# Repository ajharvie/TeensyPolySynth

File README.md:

A digital polysynth based on the teensy 4.1

Code heavily adapted from  Albert Nyström's 6-voice teensy synth: https://github.com/albnys/TeensyPoly6

I'll write up the new features and improvements at some point but I promise it's dead good

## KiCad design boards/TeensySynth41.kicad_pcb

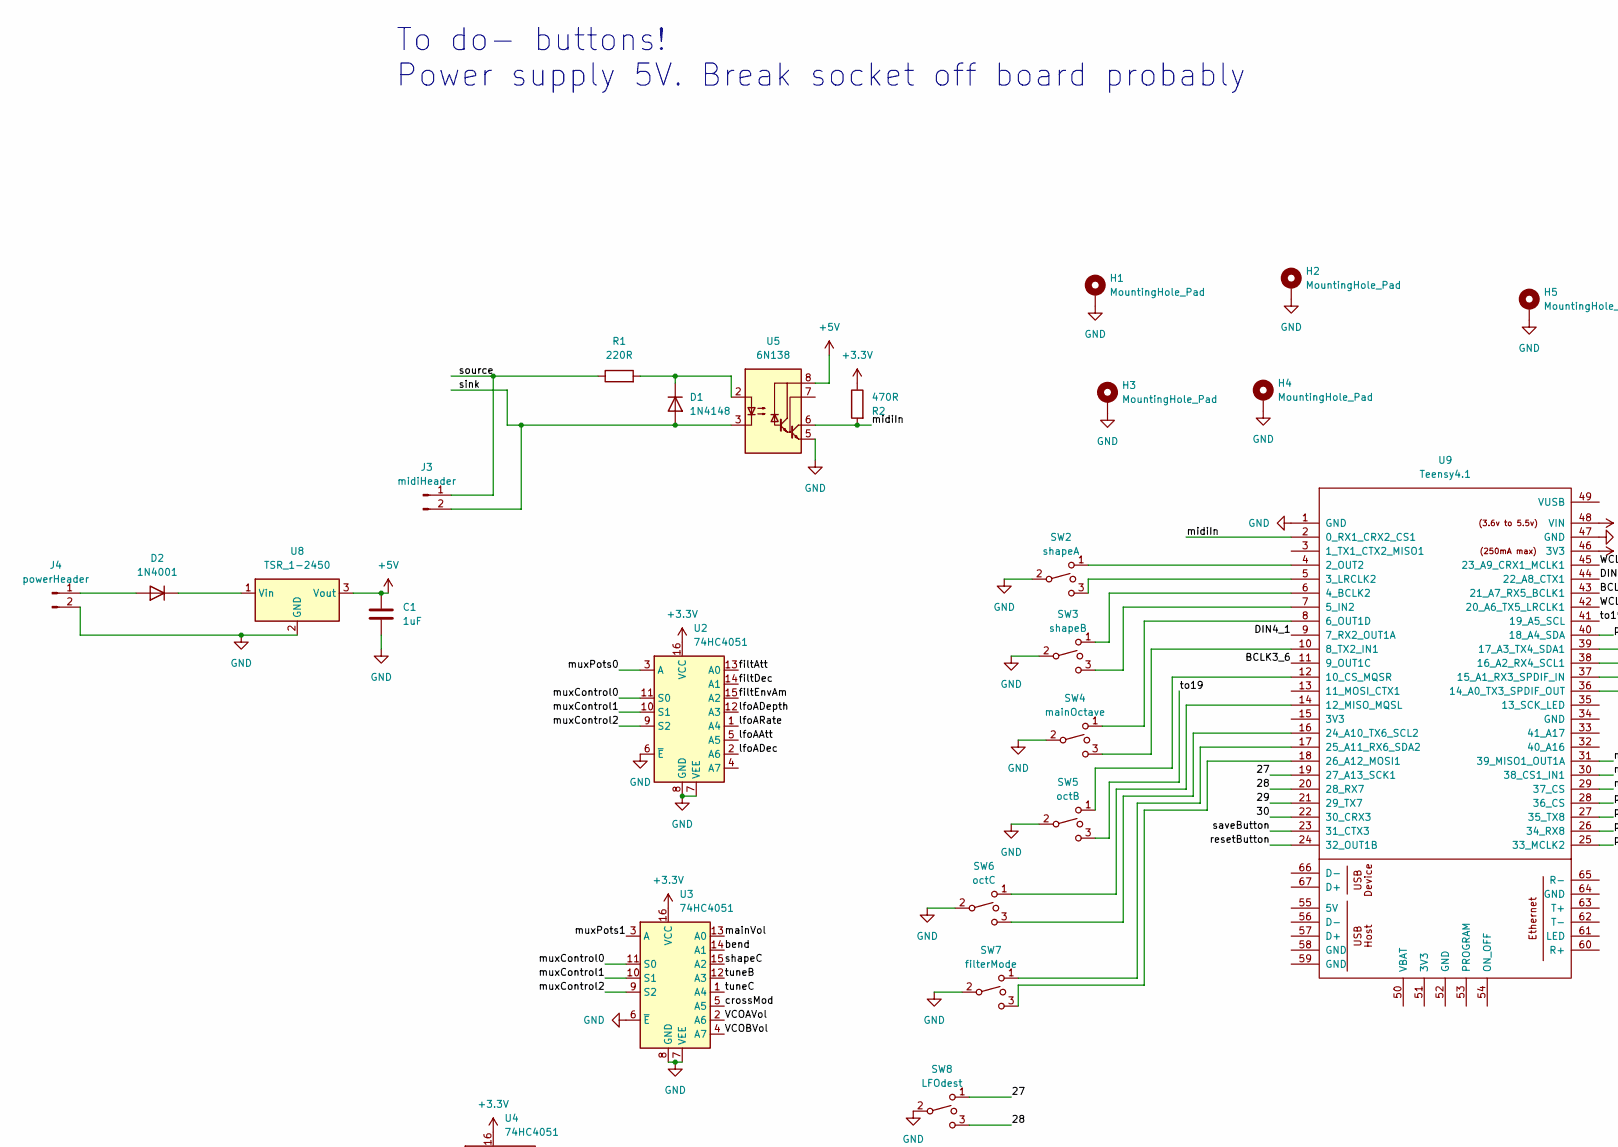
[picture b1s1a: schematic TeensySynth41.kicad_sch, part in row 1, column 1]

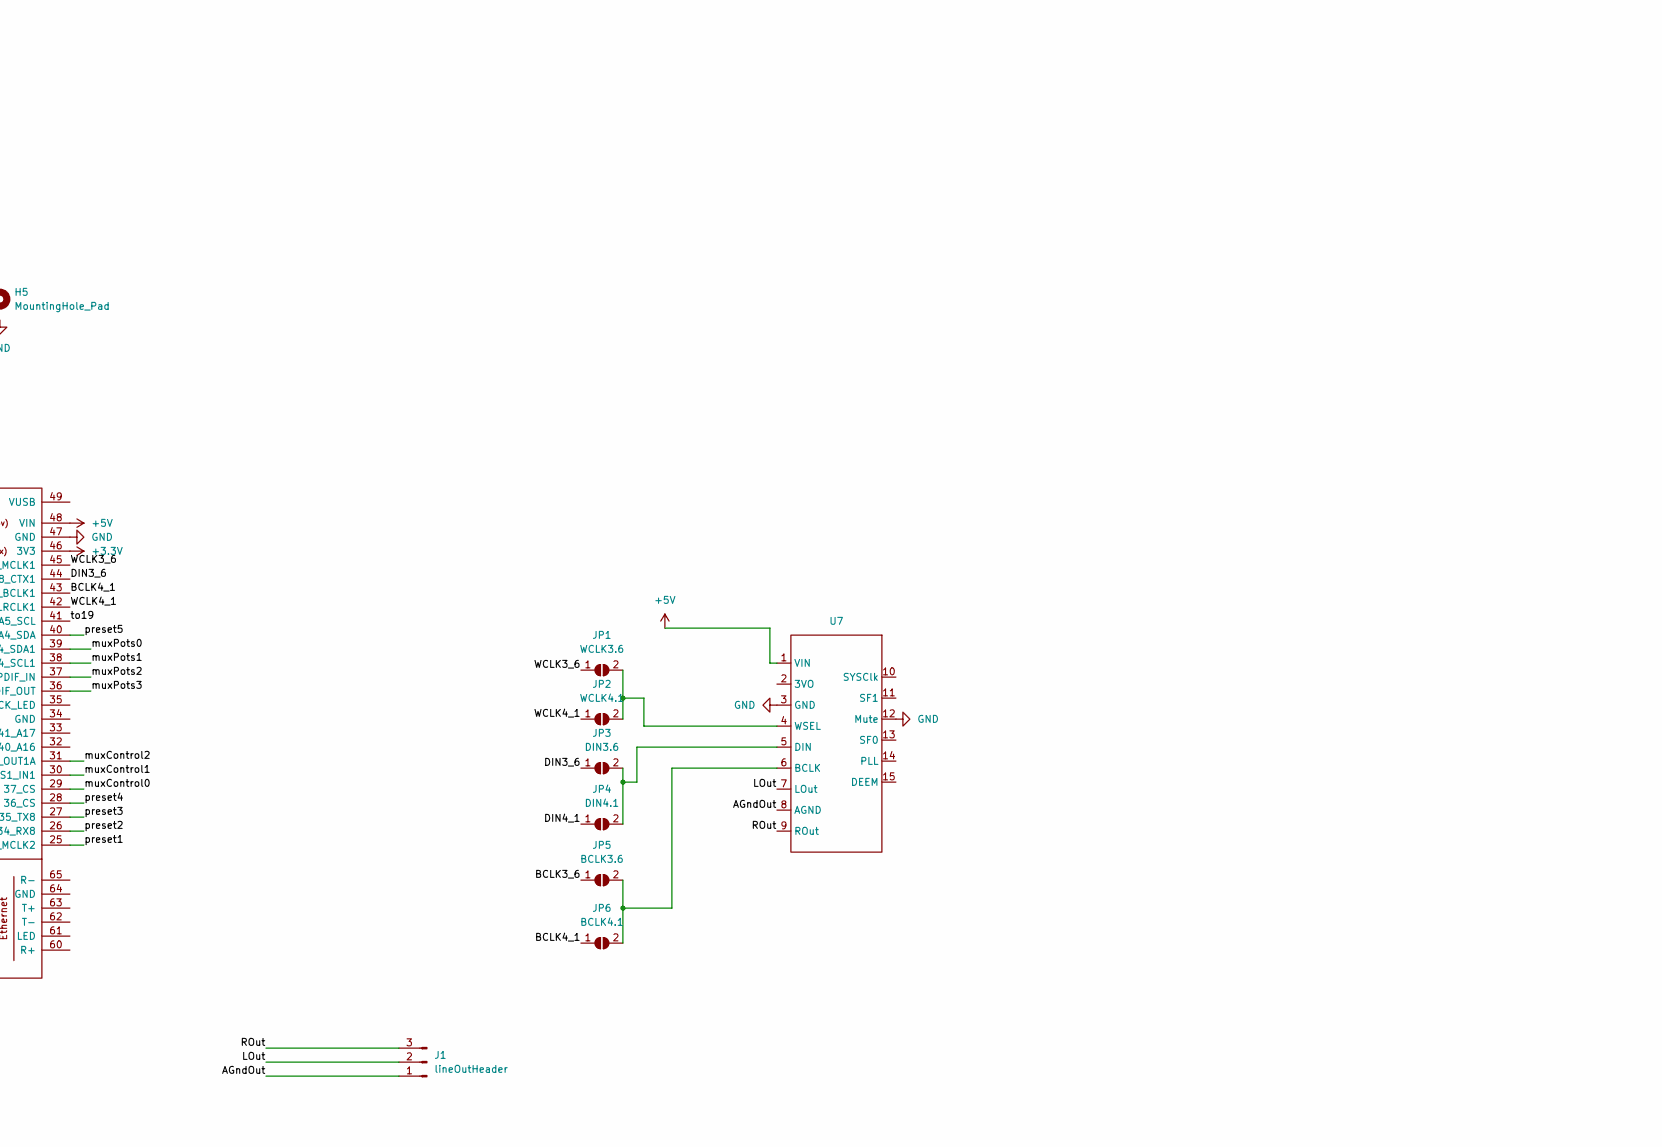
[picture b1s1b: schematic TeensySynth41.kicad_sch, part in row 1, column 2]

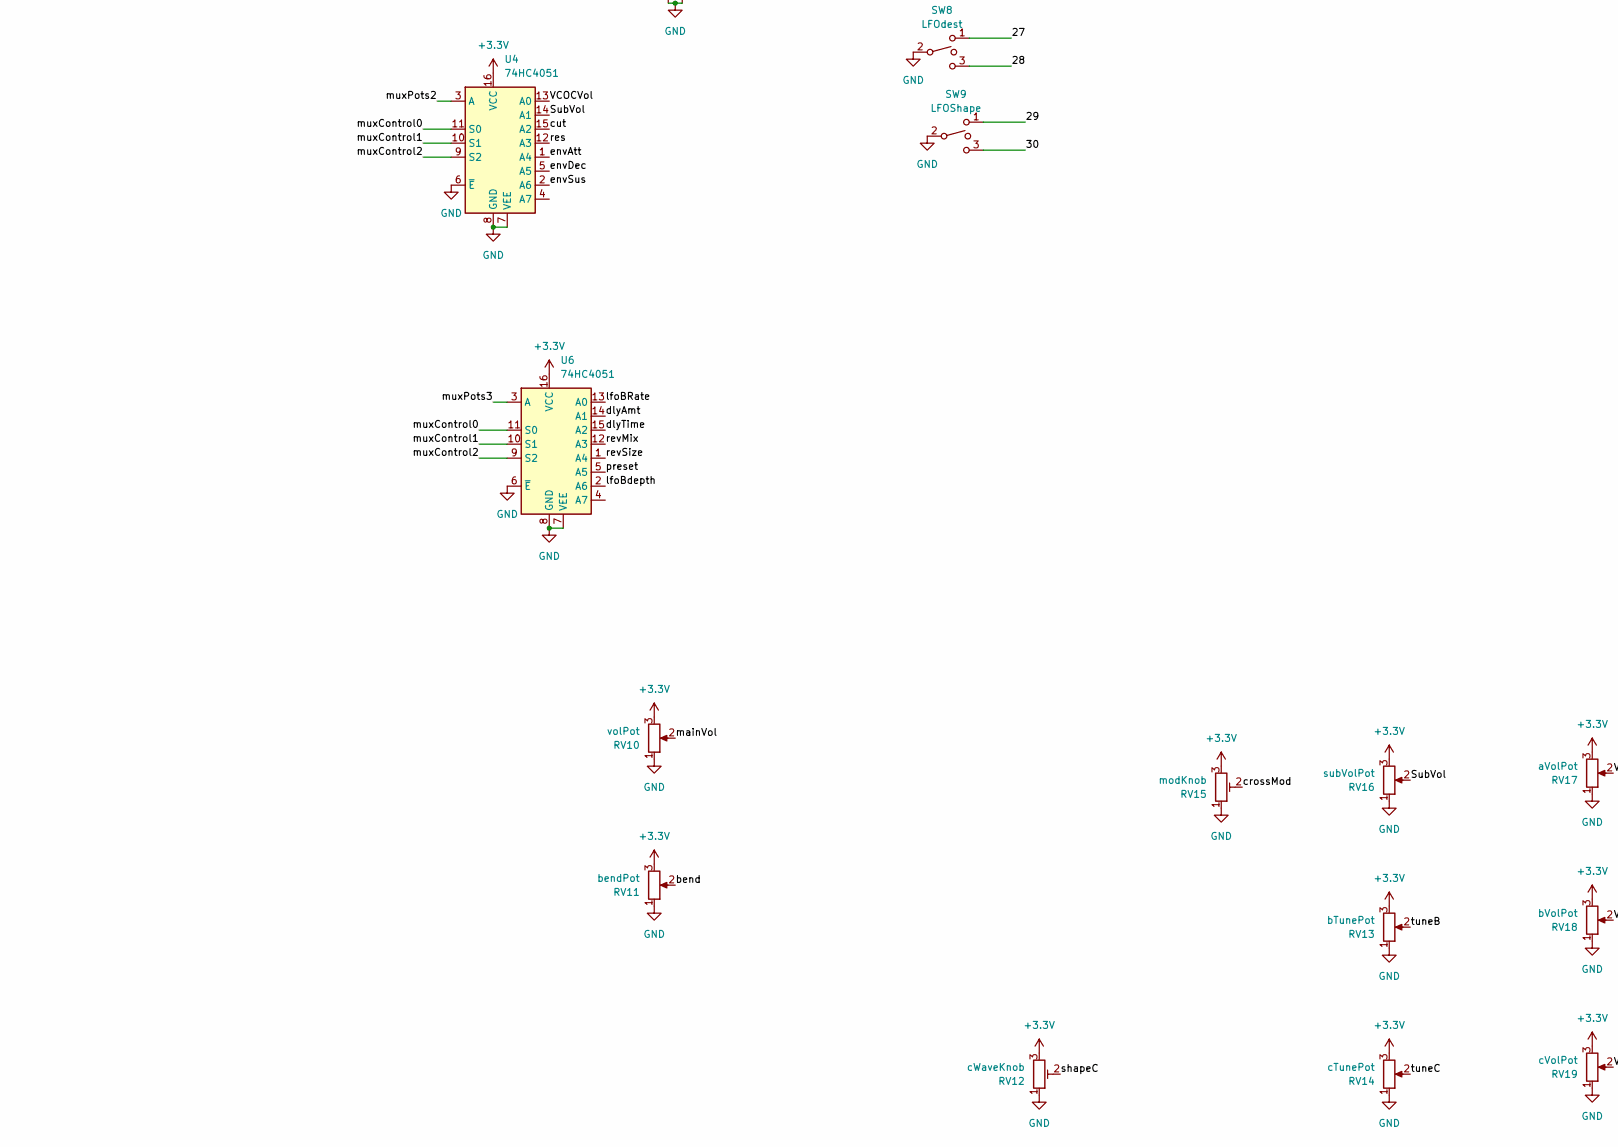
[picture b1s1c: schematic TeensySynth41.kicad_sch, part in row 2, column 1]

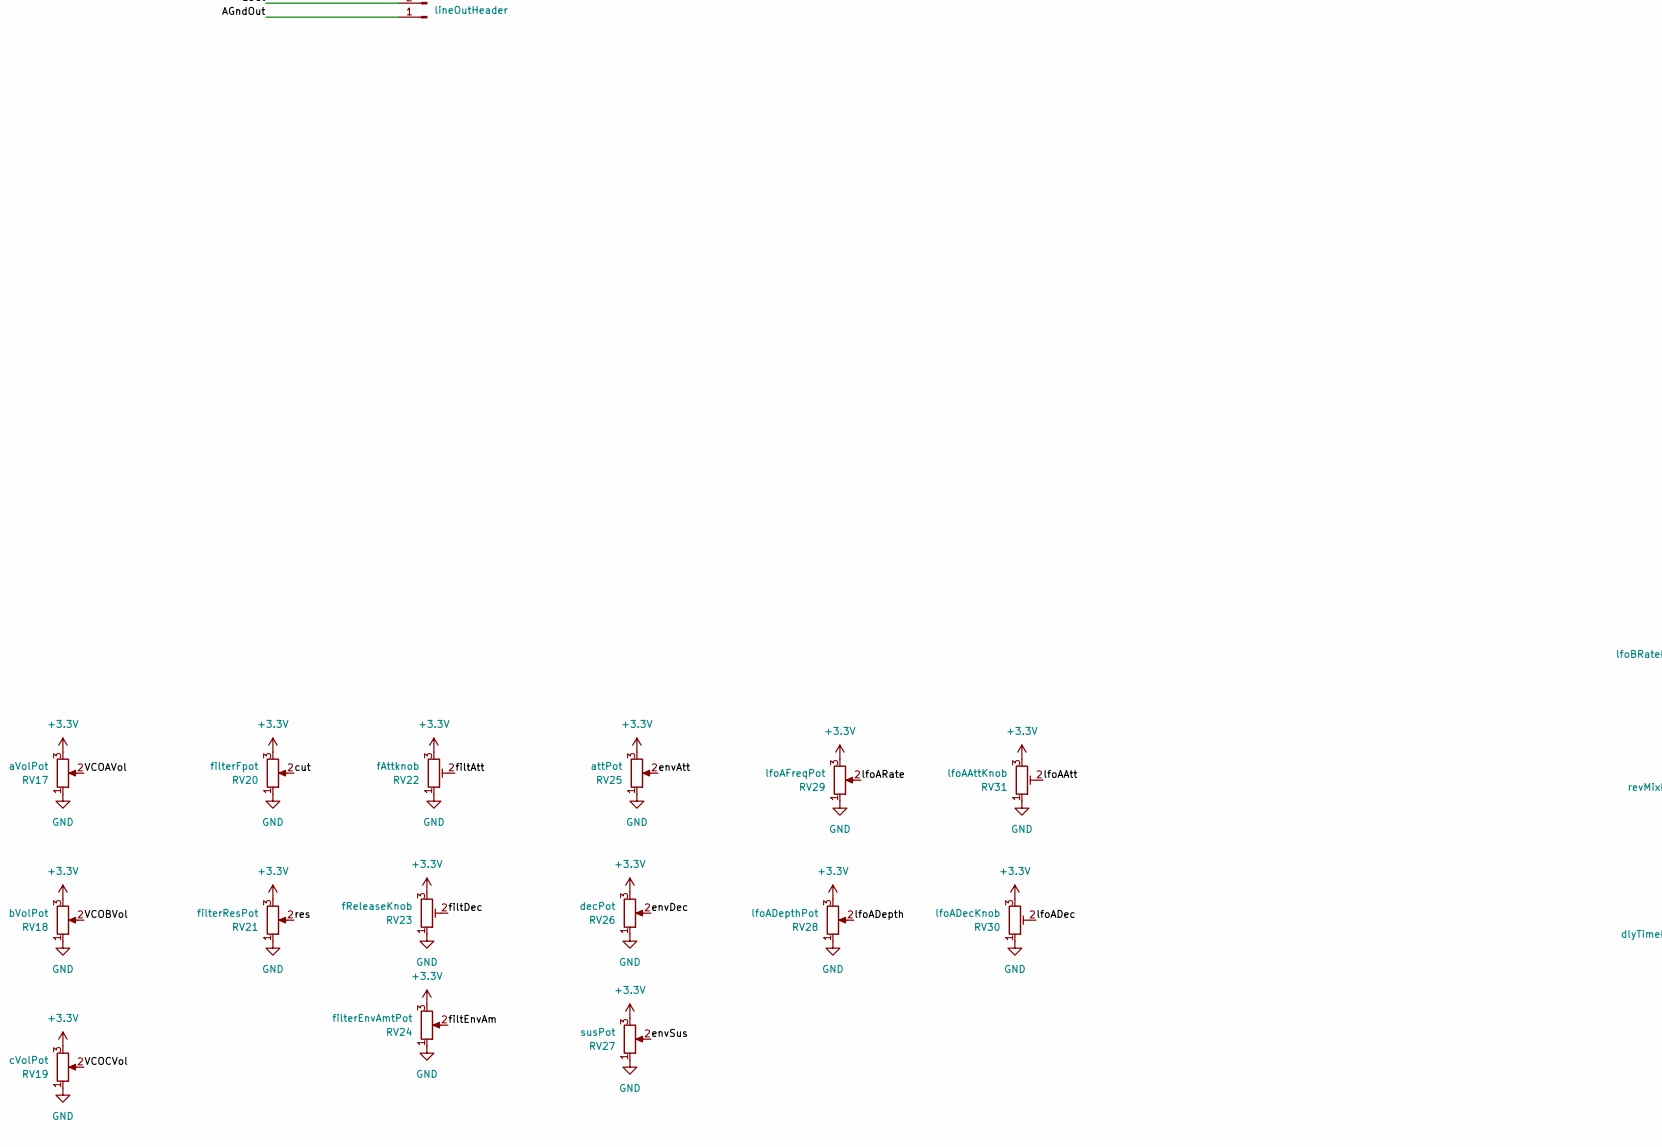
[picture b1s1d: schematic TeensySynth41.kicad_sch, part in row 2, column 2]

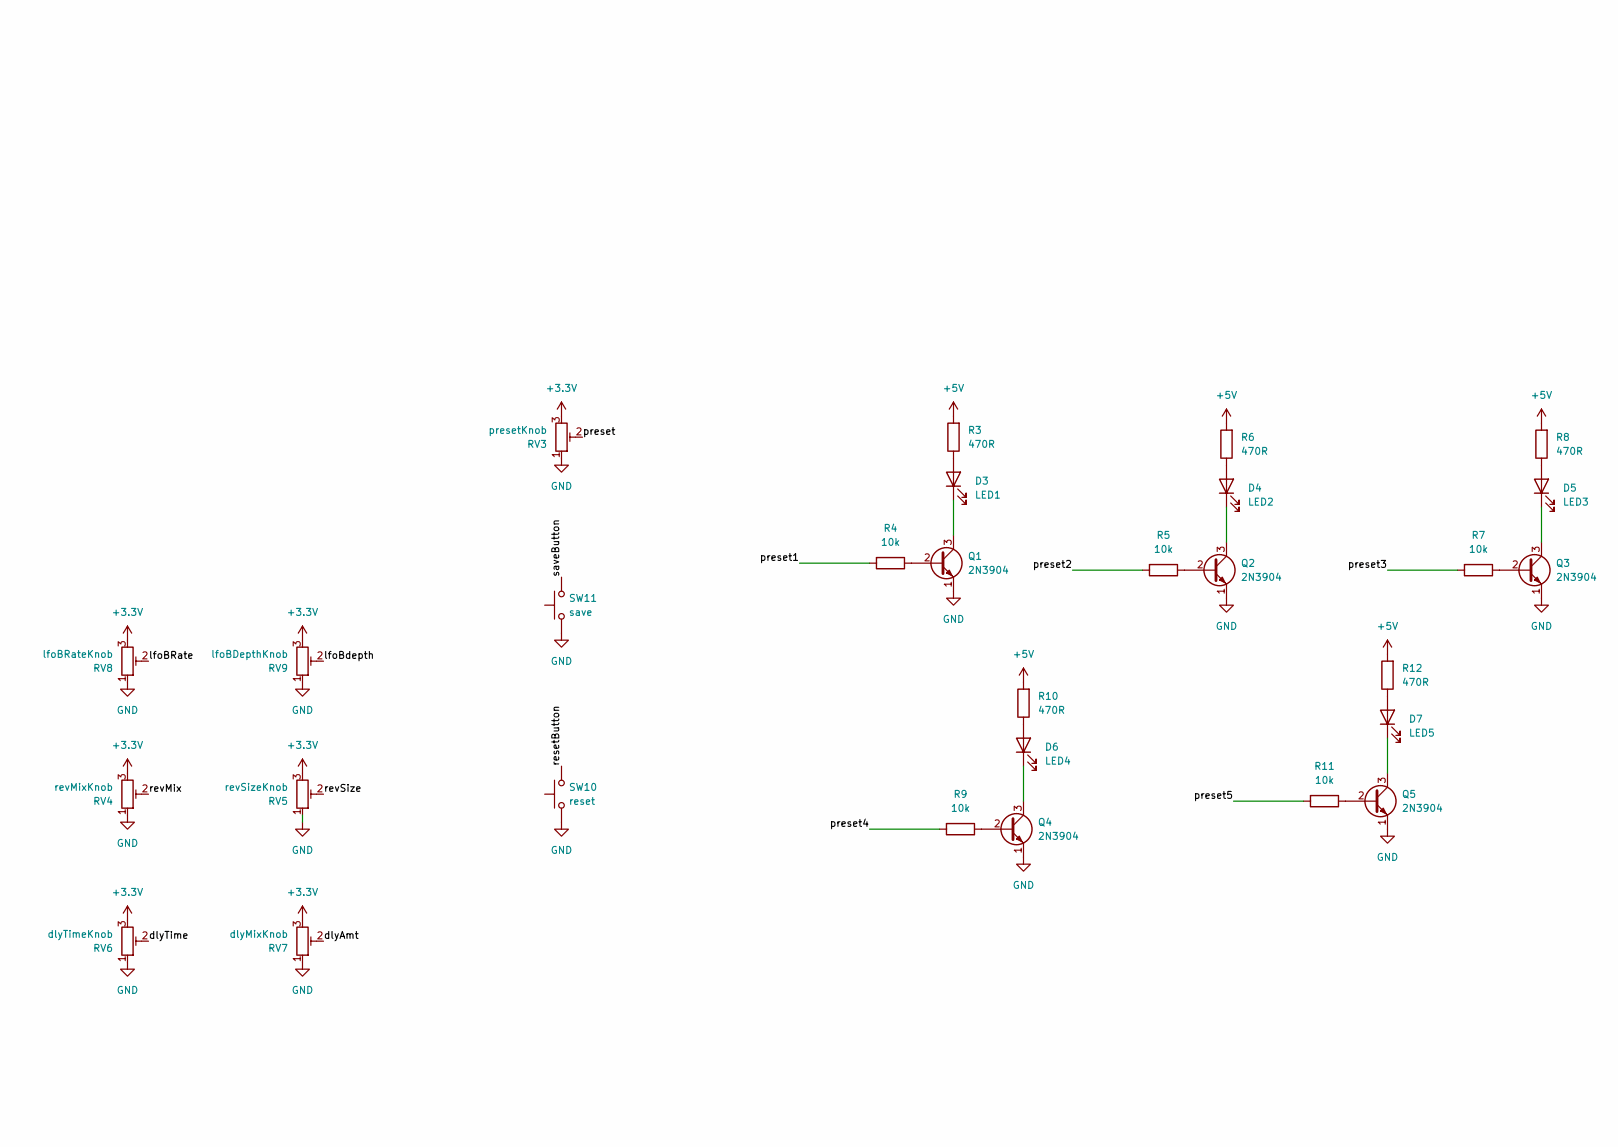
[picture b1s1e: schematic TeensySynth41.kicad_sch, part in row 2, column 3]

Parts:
C1: 1uF; C_Disc_D7.0mm_W2.5mm_P5.00mm
D1: 1N4148; D_DO-35_SOD27_P7.62mm_Horizontal
D2: 1N4001; D_DO-41_SOD81_P10.16mm_Horizontal
D3: LED1; LED_D5.0mm_FlatTop
D4: LED2; LED_D5.0mm_FlatTop
D5: LED3; LED_D5.0mm_FlatTop
D6: LED4; LED_D5.0mm_FlatTop
D7: LED5; LED_D5.0mm_FlatTop
H1, H2, H3, H4, H5: MountingHole_Pad; MountingHole_3.2mm_M3_Pad
J1: lineOutHeader; TerminalBlock_Phoenix_MPT-0,5-3-2.54_1x03_P2.54mm_Horizontal
J3: midiHeader; TerminalBlock_Phoenix_MPT-0,5-2-2.54_1x02_P2.54mm_Horizontal
J4: powerHeader; TerminalBlock_Phoenix_MPT-0,5-2-2.54_1x02_P2.54mm_Horizontal
JP1: WCLK3.6; SolderJumper-2_P1.3mm_Open_Pad1.0x1.5mm
JP2: WCLK4.1; SolderJumper-2_P1.3mm_Open_Pad1.0x1.5mm
JP3: DIN3.6; SolderJumper-2_P1.3mm_Open_Pad1.0x1.5mm
JP4: DIN4.1; SolderJumper-2_P1.3mm_Open_Pad1.0x1.5mm
JP5: BCLK3.6; SolderJumper-2_P1.3mm_Open_Pad1.0x1.5mm
JP6: BCLK4.1; SolderJumper-2_P1.3mm_Open_Pad1.0x1.5mm
Q1, Q2, Q3, Q4, Q5: 2N3904; TO-92_Inline
R1: 220R; R_Axial_DIN0207_L6.3mm_D2.5mm_P7.62mm_Horizontal
R2, R3, R6, R8, R10, R12: 470R; R_Axial_DIN0207_L6.3mm_D2.5mm_P7.62mm_Horizontal
R4, R5, R7, R9, R11: 10k; R_Axial_DIN0207_L6.3mm_D2.5mm_P7.62mm_Horizontal
RV3: presetKnob; R0904N_newholes
RV4: revMixKnob; R0904N_newholes
RV5: revSizeKnob; R0904N_newholes
RV6: dlyTimeKnob; R0904N_newholes
RV7: dlyMixKnob; R0904N_newholes
RV8: lfoBRateKnob; R0904N_newholes
RV9: lfoBDepthKnob; R0904N_newholes
RV10: volPot; alphaPot_Centred
RV11: bendPot; alphaPot_Centred
RV12: cWaveKnob; R0904N_newholes
RV13: bTunePot; alphaPot_Centred
RV14: cTunePot; alphaPot_Centred
RV15: modKnob; R0904N_newholes
RV16: subVolPot; alphaPot_Centred
RV17: aVolPot; alphaPot_Centred
RV18: bVolPot; alphaPot_Centred
RV19: cVolPot; alphaPot_Centred
RV20: filterFpot; alphaPot_Centred
RV21: filterResPot; alphaPot_Centred
RV22: fAttknob; R0904N_newholes
RV23: fReleaseKnob; R0904N_newholes
RV24: filterEnvAmtPot; alphaPot_Centred
RV25: attPot; alphaPot_Centred
RV26: decPot; alphaPot_Centred
RV27: susPot; alphaPot_Centred
RV28: lfoADepthPot; alphaPot_Centred
RV29: lfoAFreqPot; alphaPot_Centred
RV30: lfoADecKnob; R0904N_newholes
RV31: lfoAAttKnob; R0904N_newholes
SW2: shapeA; miniToggle
SW3: shapeB; miniToggle
SW4: mainOctave; miniToggle
SW5: octB; miniToggle
SW6: octC; miniToggle
SW7: filterMode; miniToggle
SW8: LFOdest; miniToggle
SW9: LFOShape; miniToggle
SW10: reset; pushButtonEuro
SW11: save; pushButtonEuro
U2, U3, U4, U6: 74HC4051; DIP-16_W7.62mm
U5: 6N138; DIP-8_W7.62mm
U7: 1334ABreakout
U8: TSR_1-2450; Converter_DCDC_TRACO_TSR-1_THT
U9: Teensy4.1; Teensy41

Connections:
+3.3V: R2.1, RV3.3, RV4.3, RV5.3, RV6.3, RV7.3, RV8.3, RV9.3, RV10.3, RV11.3, RV12.3, RV13.3, RV14.3, RV15.3, RV16.3, RV17.3, RV18.3, RV19.3, RV20.3, RV21.3, RV22.3, RV23.3, RV24.3, RV25.3, RV26.3, RV27.3, RV28.3, RV29.3, RV30.3, RV31.3, U2.16 (VCC), U3.16 (VCC), U4.16 (VCC), U6.16 (VCC), U9.46 (3V3)
+5V: C1.1, R3.2, R6.2, R8.2, R10.2, R12.2, U5.8 (VCC), U7.1 (VIN), U8.3 (Vout), U9.48 (VIN)
/27: SW8.1, U9.19 (27_A13_SCK1)
/28: SW8.3, U9.20 (28_RX7)
/29: SW9.1, U9.21 (29_TX7)
/30: SW9.3, U9.22 (30_CRX3)
/AGndOut: J1.1, U7.8 (AGND)
/BCLK3_6: JP5.1 (A), U9.11 (9_OUT1C)
/BCLK4_1: JP6.1 (A), U9.43 (21_A7_RX5_BCLK1)
/DIN3_6: JP3.1 (A), U9.44 (22_A8_CTX1)
/DIN4_1: JP4.1 (A), U9.9 (7_RX2_OUT1A)
/LOut: J1.2, U7.7 (LOut)
/ROut: J1.3, U7.9 (ROut)
/SubVol: RV16.2, U4.14 (A1)
/VCOAVol: RV17.2, U3.2 (A6)
/VCOBVol: RV18.2, U3.4 (A7)
/VCOCVol: RV19.2, U4.13 (A0)
/WCLK3_6: JP1.1 (A), U9.45 (23_A9_CRX1_MCLK1)
/WCLK4_1: JP2.1 (A), U9.42 (20_A6_TX5_LRCLK1)
/bend: RV11.2, U3.14 (A1)
/crossMod: RV15.2, U3.5 (A5)
/cut: RV20.2, U4.15 (A2)
/dlyAmt: RV7.2, U6.14 (A1)
/dlyTime: RV6.2, U6.15 (A2)
/envAtt: RV25.2, U4.1 (A4)
/envDec: RV26.2, U4.5 (A5)
/envSus: RV27.2, U4.2 (A6)
/filtAtt: RV22.2, U2.13 (A0)
/filtDec: RV23.2, U2.14 (A1)
/filtEnvAm: RV24.2, U2.15 (A2)
/lfoAAtt: RV31.2, U2.5 (A5)
/lfoADec: RV30.2, U2.2 (A6)
/lfoADepth: RV28.2, U2.12 (A3)
/lfoARate: RV29.2, U2.1 (A4)
/lfoBRate: RV8.2, U6.13 (A0)
/lfoBdepth: RV9.2, U6.2 (A6)
/mainVol: RV10.2, U3.13 (A0)
/midiIn: R2.2, U5.6 (VO2), U9.2 (0_RX1_CRX2_CS1)
/muxControl0: U2.11 (S0), U3.11 (S0), U4.11 (S0), U6.11 (S0), U9.29 (37_CS)
/muxControl1: U2.10 (S1), U3.10 (S1), U4.10 (S1), U6.10 (S1), U9.30 (38_CS1_IN1)
/muxControl2: U2.9 (S2), U3.9 (S2), U4.9 (S2), U6.9 (S2), U9.31 (39_MISO1_OUT1A)
/muxPots0: U2.3 (A), U9.39 (17_A3_TX4_SDA1)
/muxPots1: U3.3 (A), U9.38 (16_A2_RX4_SCL1)
/muxPots2: U4.3 (A), U9.37 (15_A1_RX3_SPDIF_IN)
/muxPots3: U6.3 (A), U9.36 (14_A0_TX3_SPDIF_OUT)
/preset: RV3.2, U6.5 (A5)
/preset1: R4.2, U9.25 (33_MCLK2)
/preset2: R5.2, U9.26 (34_RX8)
/preset3: R7.2, U9.27 (35_TX8)
/preset4: R9.2, U9.28 (36_CS)
/preset5: R11.2, U9.40 (18_A4_SDA)
/res: RV21.2, U4.12 (A3)
/resetButton: SW10.2, U9.24 (32_OUT1B)
/revMix: RV4.2, U6.12 (A3)
/revSize: RV5.2, U6.1 (A4)
/saveButton: SW11.2, U9.23 (31_CTX3)
/shapeC: RV12.2, U3.15 (A2)
/sink: D1.2 (A), J3.2, U5.3 (C2)
/source: J3.1, R1.1
/to19: SW5.3, U9.41 (19_A5_SCL)
/tuneB: RV13.2, U3.12 (A3)
/tuneC: RV14.2, U3.1 (A4)
GND: C1.2, H1.1, H2.1, H3.1, H4.1, H5.1, J4.2, Q1.1 (E), Q2.1 (E), Q3.1 (E), Q4.1 (E), Q5.1 (E), RV3.1, RV4.1, RV5.1, RV6.1, RV7.1, RV8.1, RV9.1, RV10.1, RV11.1, RV12.1, RV13.1, RV14.1, RV15.1, RV16.1, RV17.1, RV18.1, RV19.1, RV20.1, RV21.1, RV22.1, RV23.1, RV24.1, RV25.1, RV26.1, RV27.1, RV28.1, RV29.1, RV30.1, RV31.1, SW2.2, SW3.2, SW4.2, SW5.2, SW6.2, SW7.2, SW8.2, SW9.2, SW10.1, SW11.1, U2.6 (~E), U2.7 (VEE), U2.8 (GND), U3.6 (~E), U3.7 (VEE), U3.8 (GND), U4.6 (~E), U4.7 (VEE), U4.8 (GND), U5.5 (GND), U6.6 (~E), U6.7 (VEE), U6.8 (GND), U7.3 (GND), U7.12 (Mute), U8.2 (GND), U9.1 (GND), U9.47 (GND)
unnamed: D1.1 (K), R1.2, U5.2 (C1)
unnamed: D2.2 (A), J4.1
unnamed: D2.1 (K), U8.1 (Vin)
unnamed: D3.2 (A), R3.1
unnamed: D3.1 (K), Q1.3 (C)
unnamed: D4.2 (A), R6.1
unnamed: D4.1 (K), Q2.3 (C)
unnamed: D5.2 (A), R8.1
unnamed: D5.1 (K), Q3.3 (C)
unnamed: D6.2 (A), R10.1
unnamed: D6.1 (K), Q4.3 (C)
unnamed: D7.2 (A), R12.1
unnamed: D7.1 (K), Q5.3 (C)
unnamed: JP1.2 (B), JP2.2 (B), U7.4 (WSEL)
unnamed: JP3.2 (B), JP4.2 (B), U7.5 (DIN)
unnamed: JP5.2 (B), JP6.2 (B), U7.6 (BCLK)
unnamed: Q1.2 (B), R4.1
unnamed: Q2.2 (B), R5.1
unnamed: Q3.2 (B), R7.1
unnamed: Q4.2 (B), R9.1
unnamed: Q5.2 (B), R11.1
unnamed: SW2.1, U9.4 (2_OUT2)
unnamed: SW2.3, U9.5 (3_LRCLK2)
unnamed: SW3.1, U9.6 (4_BCLK2)
unnamed: SW3.3, U9.7 (5_IN2)
unnamed: SW4.1, U9.8 (6_OUT1D)
unnamed: SW4.3, U9.10 (8_TX2_IN1)
unnamed: SW5.1, U9.12 (10_CS_MQSR)
unnamed: SW6.1, U9.14 (12_MISO_MQSL)
unnamed: SW6.3, U9.16 (24_A10_TX6_SCL2)
unnamed: SW7.1, U9.17 (25_A11_RX6_SDA2)
unnamed: SW7.3, U9.18 (26_A12_MOSI1)

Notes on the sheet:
To do- buttons! Power supply 5V. Break socket off board probably

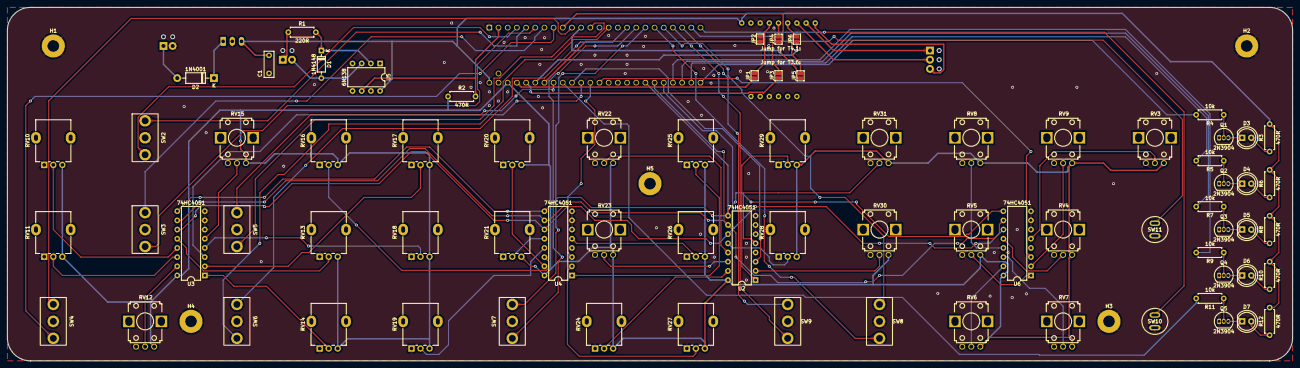
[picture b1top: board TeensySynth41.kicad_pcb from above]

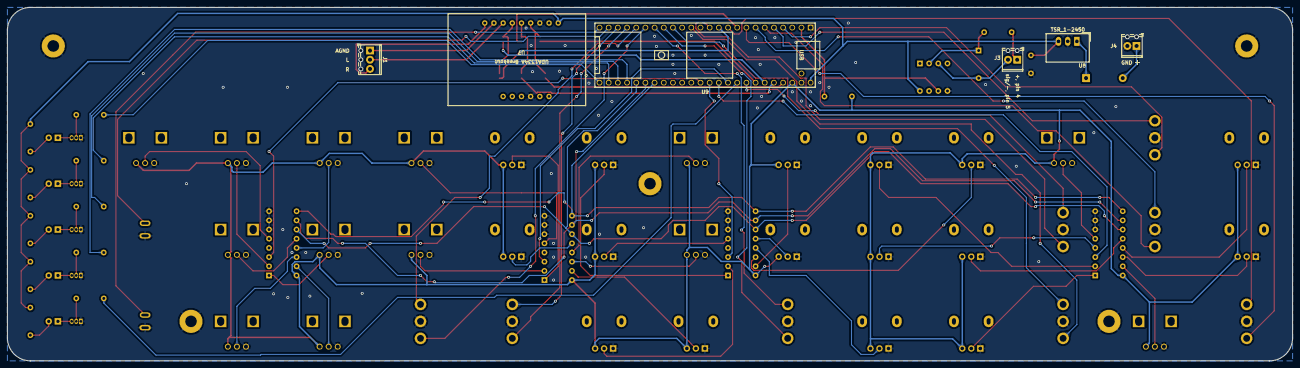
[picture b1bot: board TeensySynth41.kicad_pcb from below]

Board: 2 copper layers, 355.6 x 97.8 mm, 86 parts (6 on the bottom side), 95 nets.

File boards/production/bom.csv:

Designator,Footprint,Quantity,Value,LCSC Part #
C1,C_Disc_D7.0mm_W2.5mm_P5.00mm,1,1uF,
D1,D_DO-35_SOD27_P7.62mm_Horizontal,1,1N4148,
D2,D_DO-41_SOD81_P10.16mm_Horizontal,1,1N4001,
D3,LED_D5.0mm_FlatTop,1,LED1,
D4,LED_D5.0mm_FlatTop,1,LED2,
D5,LED_D5.0mm_FlatTop,1,LED3,
D6,LED_D5.0mm_FlatTop,1,LED4,
D7,LED_D5.0mm_FlatTop,1,LED5,
"H1, H2, H3, H4, H5",MountingHole_3.2mm_M3_Pad,5,MountingHole_Pad,
J1,"TerminalBlock_Phoenix_MPT-0,5-3-2.54_1x03_P2.54mm_Horizontal",1,lineOutHeader,
J3,"TerminalBlock_Phoenix_MPT-0,5-2-2.54_1x02_P2.54mm_Horizontal",1,midiHeader,
J4,"TerminalBlock_Phoenix_MPT-0,5-2-2.54_1x02_P2.54mm_Horizontal",1,powerHeader,
JP1,SolderJumper-2_P1.3mm_Open_Pad1.0x1.5mm,1,WCLK3.6,
JP2,SolderJumper-2_P1.3mm_Open_Pad1.0x1.5mm,1,WCLK4.1,
JP3,SolderJumper-2_P1.3mm_Open_Pad1.0x1.5mm,1,DIN3.6,
JP4,SolderJumper-2_P1.3mm_Open_Pad1.0x1.5mm,1,DIN4.1,
JP5,SolderJumper-2_P1.3mm_Open_Pad1.0x1.5mm,1,BCLK3.6,
JP6,SolderJumper-2_P1.3mm_Open_Pad1.0x1.5mm,1,BCLK4.1,
"Q1, Q2, Q3, Q4, Q5",TO-92_Inline,5,2N3904,
R1,R_Axial_DIN0207_L6.3mm_D2.5mm_P7.62mm_Horizontal,1,220R,
"R10, R12, R2, R3, R6, R8",R_Axial_DIN0207_L6.3mm_D2.5mm_P7.62mm_Horizontal,6,470R,
"R11, R4, R5, R7, R9",R_Axial_DIN0207_L6.3mm_D2.5mm_P7.62mm_Horizontal,5,10k,
RV10,alphaPot_Centred,1,volPot,
RV11,alphaPot_Centred,1,bendPot,
RV12,R0904N_newholes,1,cWaveKnob,
RV13,alphaPot_Centred,1,bTunePot,
RV14,alphaPot_Centred,1,cTunePot,
RV15,R0904N_newholes,1,modKnob,
RV16,alphaPot_Centred,1,subVolPot,
RV17,alphaPot_Centred,1,aVolPot,
RV18,alphaPot_Centred,1,bVolPot,
RV19,alphaPot_Centred,1,cVolPot,
RV20,alphaPot_Centred,1,filterFpot,
RV21,alphaPot_Centred,1,filterResPot,
RV22,R0904N_newholes,1,fAttknob,
RV23,R0904N_newholes,1,fReleaseKnob,
RV24,alphaPot_Centred,1,filterEnvAmtPot,
RV25,alphaPot_Centred,1,attPot,
RV26,alphaPot_Centred,1,decPot,
RV27,alphaPot_Centred,1,susPot,
RV28,alphaPot_Centred,1,lfoADepthPot,
RV29,alphaPot_Centred,1,lfoAFreqPot,
RV3,R0904N_newholes,1,presetKnob,
RV30,R0904N_newholes,1,lfoADecKnob,
RV31,R0904N_newholes,1,lfoAAttKnob,
RV4,R0904N_newholes,1,revMixKnob,
RV5,R0904N_newholes,1,revSizeKnob,
RV6,R0904N_newholes,1,dlyTimeKnob,
RV7,R0904N_newholes,1,dlyMixKnob,
RV8,R0904N_newholes,1,lfoBRateKnob,
RV9,R0904N_newholes,1,lfoBDepthKnob,
SW10,pushButtonEuro,1,reset,
SW11,pushButtonEuro,1,save,
SW2,miniToggle,1,shapeA,
SW3,miniToggle,1,shapeB,
SW4,miniToggle,1,mainOctave,
SW5,miniToggle,1,octB,
SW6,miniToggle,1,octC,
SW7,miniToggle,1,filterMode,
SW8,miniToggle,1,LFOdest,
SW9,miniToggle,1,LFOShape,
"U2, U3, U4, U6",DIP-16_W7.62mm,4,74HC4051,
U5,DIP-8_W7.62mm,1,6N138,
U7,1334ABreakout,1,~,
U8,Converter_DCDC_TRACO_TSR-1_THT,1,TSR_1-2450,
U9,Teensy41,1,Teensy4.1,

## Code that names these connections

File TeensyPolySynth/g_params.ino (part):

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      tuneB = pow(2,(tuneB));
    }
    else{
      tuneB = 1;
    }

    
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      tuneC = pow(2,(tuneC));
    }
    else{
      tuneC = 1;
    }


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    

    if (dlyAmt < 0) {
      dlyAmt = 0;
    }

    resetting = 0;
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
    //or check for pressed "read controls/reset" button. when reset button pressed, values should take those as read on controls

    resetting = 1; //for properly resetting things to knob position on return to preset 0/non memory mode

    resetPressed = digitalRead(32);

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        tuneB = pow(2,(tuneB));
      }
      else{
        tuneB = 1;
      }
    
      oldTuneBpot = tuneBpot + tresh3 / 2;
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        tuneC = pow(2,(tuneC));
      }
      else{
        tuneC = 1;
      }
      oldTuneCpot = tuneCpot + tresh3 / 2;
      tuneCCount = 0;
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    lfoDecpot = mux6_0;
    if (oldLfoDecpot + tresh2 < lfoDecpot || oldLfoDecpot - tresh2 > lfoDecpot || resetPressed == 0) {
      //lfoAdec = 4000 * (float)mux6_0 / 1024;      
      lfoAdec = 1; //no need for decay now, just release
      lfoArel = 4000 * expLookup1024[mux6_0] / 1024 + minTime;
      oldLfoDecpot = lfoDecpot + (tresh2 / 2);
      //Serial.println("Lfo A Dec turn");
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    if (oldDlyAmtpot + tresh2 < dlyAmtpot || oldDlyAmtpot - tresh2 > dlyAmtpot || resetPressed == 0) {
      dlyAmt = (float)mux1_3 / 1100 - 0.1;
      if (dlyAmt < 0) {
        dlyAmt = 0;
      }
      oldDlyAmtpot = dlyAmtpot + tresh2 / 2;
      //Serial.println("Dly amt turn");
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
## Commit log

2024-10-31 added readme
